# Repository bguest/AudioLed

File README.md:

# AudioLed
Board to drive a string of WS2801 chips using audio and a MSGEQ7

# Setup

## Attaching FTDI
The FTDI Cable plugs in under the 12v Power Connector. The FTDI Grounds are close to the center of
the board, the DTR is closer to the edge of the board.

If the power connector is in the upper right of the board facing up the FTDI pins will be

GND, GND, VCC, RXI, RXO, DTR

## Setting up Arduino and Compiling the Code (MAC)

1. Clone this repo to `~/Documents/Arduino` with `cd ~/Documents/Arduino && git clone git@github.com:bguest/AudioLed.git`
2. Change directory to AudioLED with `cd AudioLed`
3. Mod setup script `chmod +x setup.sh`
4. Run Setup `.\setup.sh` this will clone correct versions of `Adafruit_WS2801` and `Arduino-IRremote`
5. Download Arduino v1.6.6 (May not compile with later versions of Arduino)
6. Launch Arduino v1.6.6
7. Open AudioLED
8. Set board to `Arduino Pro or Pro Mini`
9. Set processor to `ATmega328 (5V, 16MHz)`
10. Verify and Upload Code

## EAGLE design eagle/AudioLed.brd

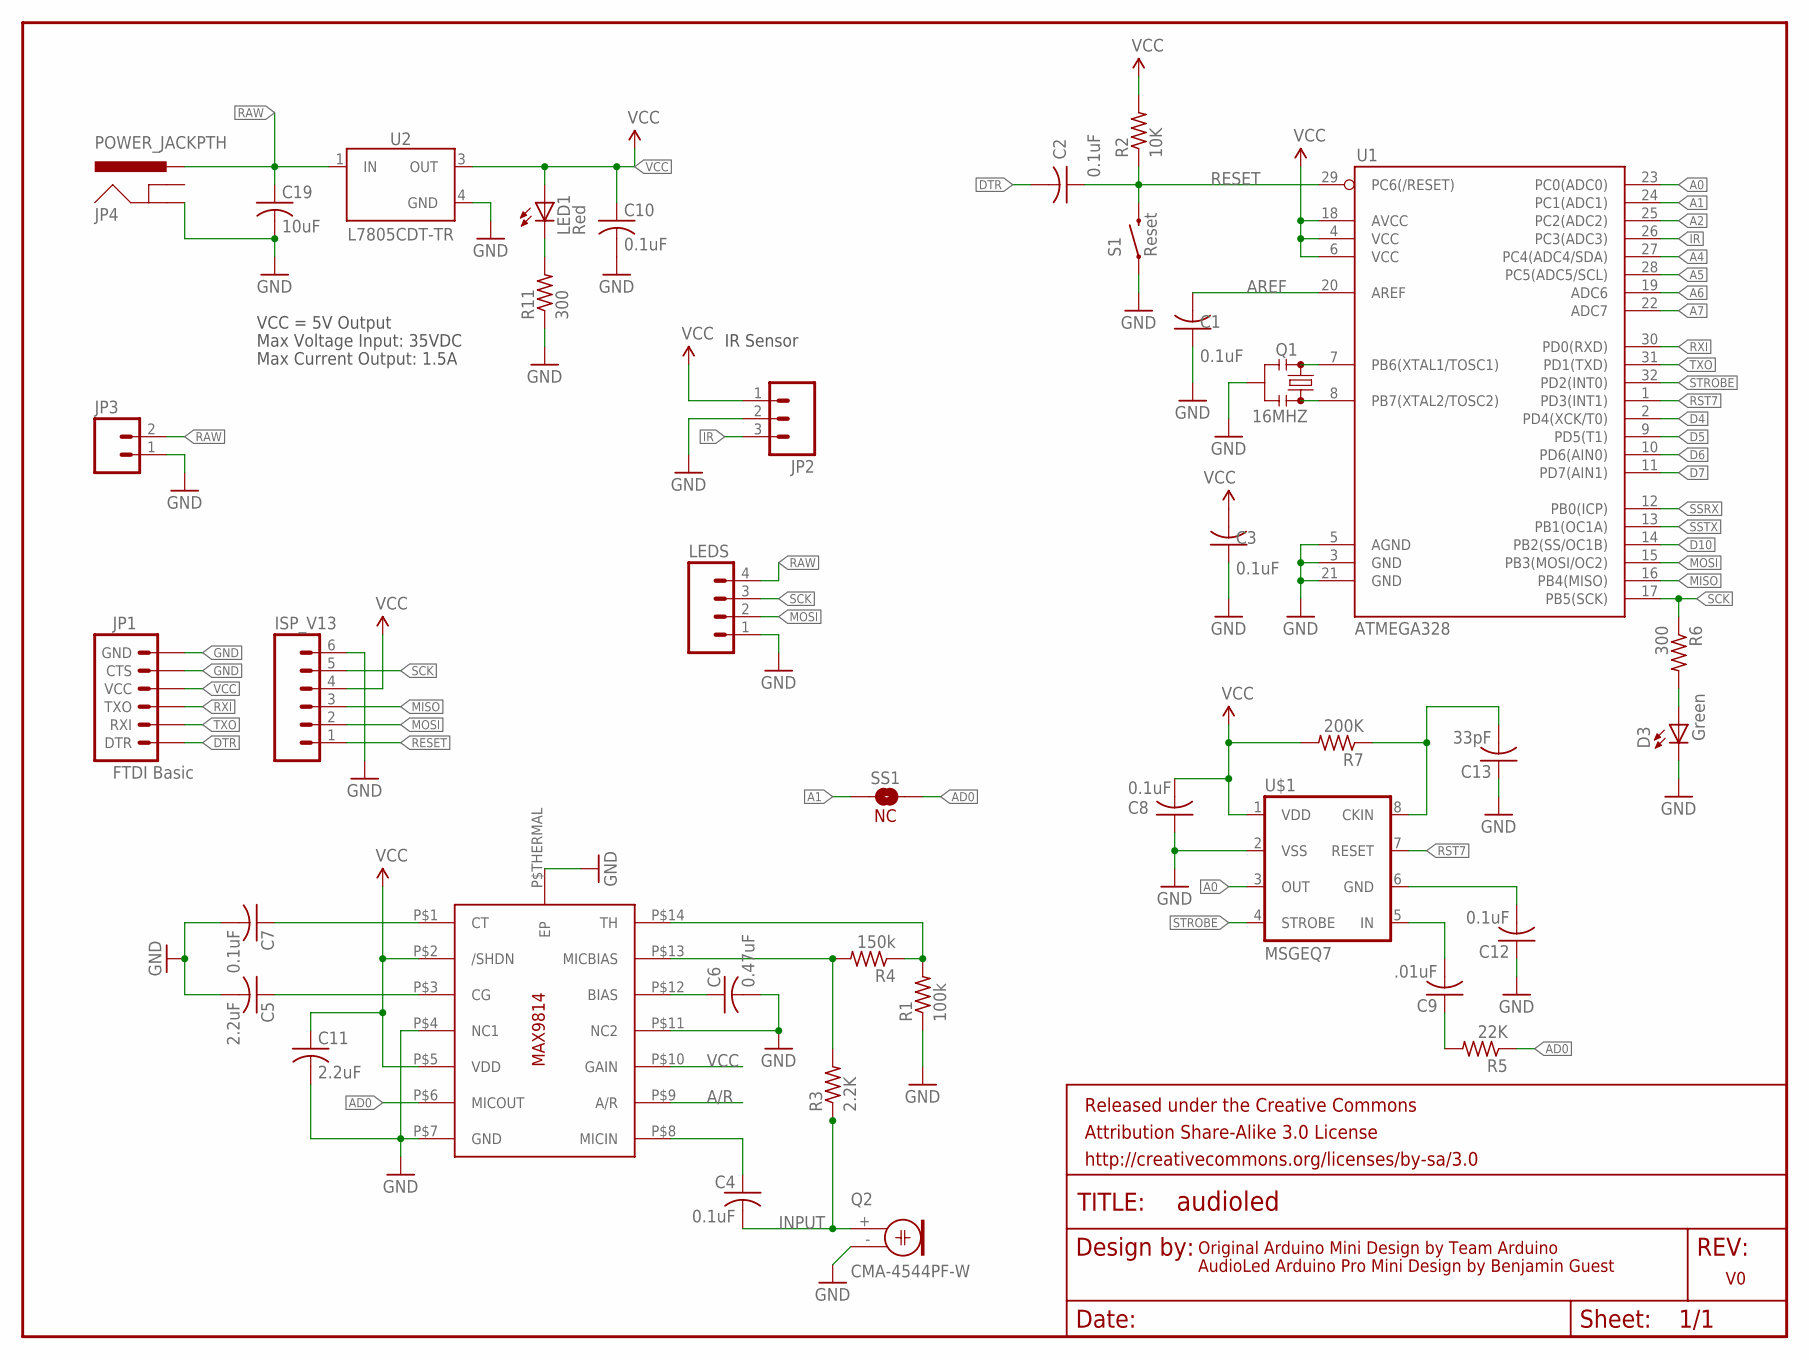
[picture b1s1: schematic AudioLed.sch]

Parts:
C1, C2, C3, C8, C10, C12: 0.1uF; C0805
C4, C7: 0.1uF; C0805K
C5, C11: 2.2uF; C0805K
C6: 0.47uF; C0805K
C9: .01uF; C0805
C13: 33pF; C0805
C19: 10uF; C0805
D3: Green; CHIPLED_0805
FRAME1: FRAME-LETTER; CREATIVE_COMMONS
ISP_V13: M06SIP; 1X06
JP1: FTDI Basic; 1X06
JP2: M03JST-PTH; JST-3-PTH
JP3: M02JST-PTH-2; JST-2-PTH
JP4: POWER_JACKPTH; POWER_JACK_PTH
LED1: Red; CHIPLED_0805
LEDS: M04JST-PTH; JST-4-PTH
Q1: 16MHZ; RESONATOR-SMD
Q2: CMA-4544PF-W; 9.7ELECTRET
R1: 100k; R0805
R2: 10K; M0805
R3: 2.2K; R0805
R4: 150k; R0805
R5: 22K; M0805
R6, R11: 300; M0805
R7: 200K; M0805
S1: Reset; TACTILE-SWITCH-SMD-ALT01
SS1: NC; SJ_2S
U1: ATMEGA328; TQFP32-08
U2: L7805CDT-TR; DPAK
U4: MAX9814TDFN14; TDFN14_3X3MM
U$1: MSGEQ7; DIL08-ROUND

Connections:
A0: U1.23 (PC0(ADC0)), U$1.3 (OUT)
A1: SS1.1, U1.24 (PC1(ADC1))
A2: U1.25 (PC2(ADC2))
A4: U1.27 (PC4(ADC4/SDA))
A5: U1.28 (PC5(ADC5/SCL))
A6: U1.19 (ADC6)
A7: U1.22 (ADC7)
A/R: U4.P$9 (A/R)
AD0: R5.1, SS1.2, U4.P$6 (MICOUT)
AREF: C1.2, U1.20 (AREF)
D4: U1.2 (PD4(XCK/T0))
D5: U1.9 (PD5(T1))
D6: U1.10 (PD6(AIN0))
D7: U1.11 (PD7(AIN1))
D10: U1.14 (PB2(SS/OC1B))
DTR: C2.2, JP1.1 (DTR)
GND: C1.1, C3.1, C5.2, C6.2, C7.2, C8.1, C10.2, C11.2, C12.1, C13.1, C19.2, D3.C, ISP_V13.6, JP1.5 (CTS), JP1.6 (GND), JP2.2, JP3.1, JP4.GND, LEDS.1, Q1.2, Q2.- (1), R1.1, R11.1, S1.1, S1.2 (1), U1.3 (GND), U1.5 (AGND), U1.21 (GND), U2.4 (GND), U4.P$4 (NC1), U4.P$7 (GND), U4.P$11 (NC2), U4.P$THERMAL (EP), U$1.2 (VSS)
INPUT: C4.2, Q2.+ (2), R3.1
IR: JP2.3, U1.26 (PC3(ADC3))
MISO: ISP_V13.3, U1.16 (PB4(MISO))
MOSI: ISP_V13.2, LEDS.2, U1.15 (PB3(MOSI/OC2))
unnamed: Q1.3, U1.8 (PB7(XTAL2/TOSC2))
unnamed: Q1.1, U1.7 (PB6(XTAL1/TOSC1))
unnamed: C6.1, U4.P$12 (BIAS)
unnamed: LED1.C, R11.2
unnamed: C4.1, U4.P$8 (MICIN)
unnamed: C9.1, R5.2
unnamed: D3.A, R6.2
unnamed: C7.1, U4.P$1 (CT)
unnamed: C5.1, U4.P$3 (CG)
unnamed: R1.2, R4.1, U4.P$14 (TH)
unnamed: R3.2, R4.2, U4.P$13 (MICBIAS)
unnamed: C9.2, U$1.5 (IN)
unnamed: C12.2, U$1.6 (GND)
unnamed: C13.2, R7.1, U$1.8 (CKIN)
RAW: C19.1, JP3.2, JP4.PWR, LEDS.4, U2.1 (IN)
RESET: C2.1, ISP_V13.1, R2.1, S1.3 (2), S1.4 (2), U1.29 (PC6(/RESET))
RST7: U1.1 (PD3(INT1)), U$1.7 (RESET)
RXI: JP1.3 (TXO), U1.30 (PD0(RXD))
SCK: ISP_V13.5, LEDS.3, R6.1, U1.17 (PB5(SCK))
SSRX: U1.12 (PB0(ICP))
SSTX: U1.13 (PB1(OC1A))
STROBE: U1.32 (PD2(INT0)), U$1.4 (STROBE)
TXO: JP1.2 (RXI), U1.31 (PD1(TXD))
VCC: C3.2, C8.2, C10.1, C11.1, ISP_V13.4, JP1.4 (VCC), JP2.1, LED1.A, R2.2, R7.2, U1.4 (VCC), U1.6 (VCC), U1.18 (AVCC), U2.3 (OUT), U4.P$2 (/SHDN), U4.P$5 (VDD), U4.P$10 (GAIN), U$1.1 (VDD)

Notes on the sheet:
Original Arduino Mini Design by Team Arduino
AudioLed Arduino Pro Mini Design by Benjamin Guest
Max Voltage Input: 35VDC
Max Current Output: 1.5A
VCC = 5V Output
IR Sensor

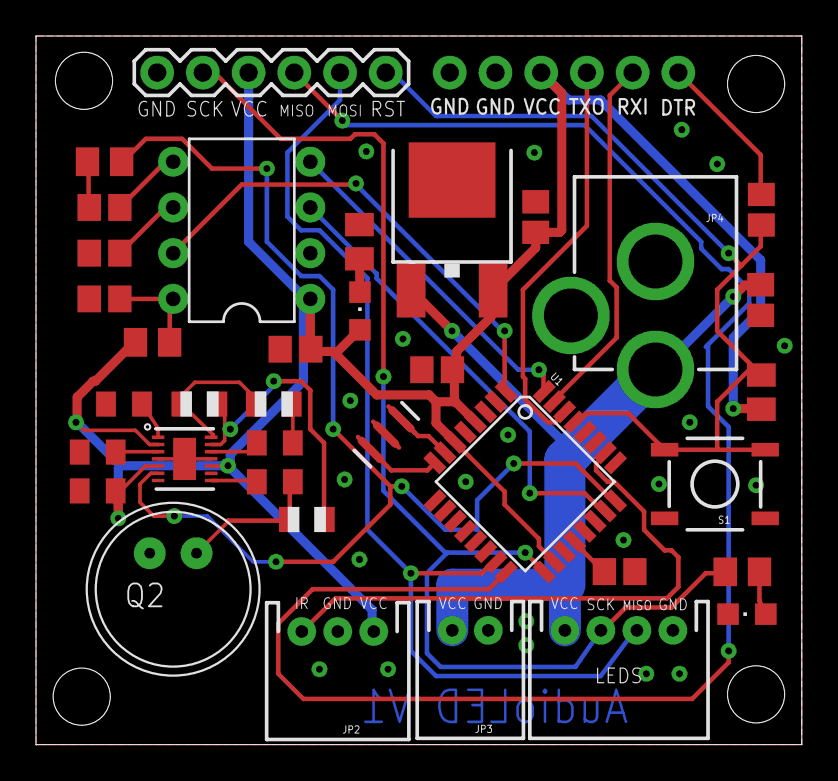
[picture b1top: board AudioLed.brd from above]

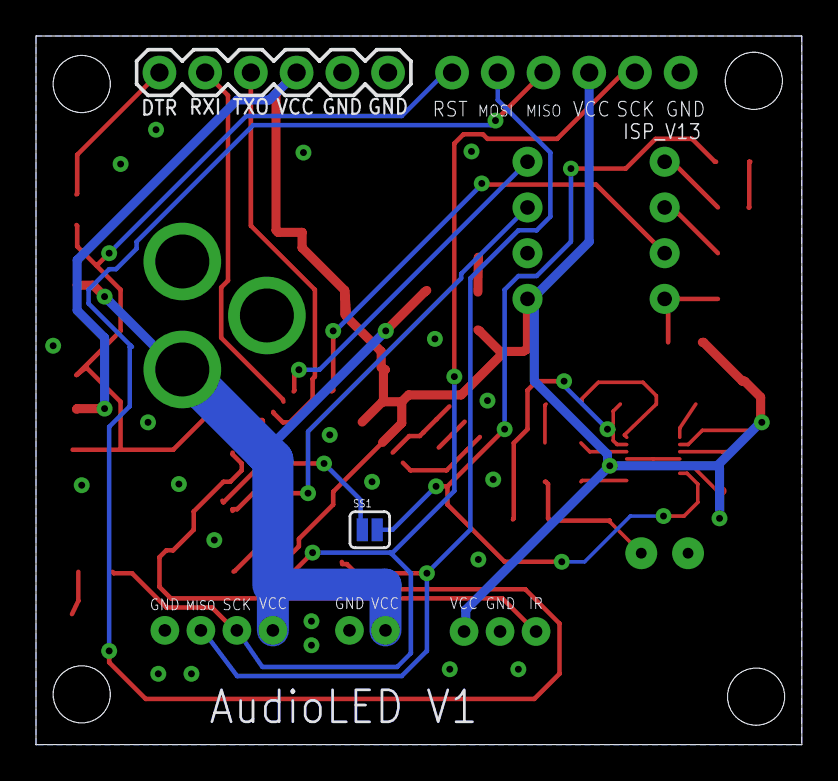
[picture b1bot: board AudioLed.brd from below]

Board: 2 copper layers, 42.5 x 39.4 mm, 39 parts (2 on the bottom side), 32 nets.

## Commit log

2016-01-05 Board
2016-01-05 Fix Incorrectly Labled Capacitor
2016-01-06 Add Dimensions
2016-01-25 Move trace slightly
2016-01-25 Replace bad resonator with SparkFun Resonator
2016-02-14 WIP: Add Code
2016-02-14 Add Sound
2016-02-15 Add Spectrum0
2016-02-16 Add Wander
2016-02-18 Add Tempo and IR
2016-02-19 Add Wave Equation
2016-02-19 Add Hue array, fix tempo button
2016-02-20 Move Remote to its own class (untested)
2016-02-21 Add Influence (untested)
2016-02-21 Add Cnter Pulse (untested)
2016-02-22 Fixes to untested
2016-02-23 Switch to hsv calculations add drizly color switch
2016-02-23 change wave boundary to neuman
2016-02-24 Add Pixel Direction
2016-02-25 Sound Collect
2016-02-25 Switch to RollOff
2016-02-25 Improvements to TwoColor
2016-03-01 Add Visual For Current Push Layer
2016-03-03 TimeDomain
2016-03-03 Tweaks
2016-03-04 Add Configurations
2016-03-11 Add Serveral new configs
2016-03-15 Add ParticleSystem
2016-03-19 Add Down Force to wave
2016-03-21 Add CellularAutomata and things
2016-04-04 Add Second Remote, Add Configs
2016-04-10 Add Strobe Effect
2016-04-10 New TwoColor input inprovements
2016-04-11 Add CenterSquare
2016-04-11 'Fix' CenterSquare
2016-04-15 Move things around
2016-04-16 Bump Board Version to V1
2016-04-19 Add USE_RAW_VOLUME
2016-04-20 Improvements to CenterSquare
2016-04-20 Simplification?
2016-04-22 Add Bubbles
2016-04-24 Fix Remote
2016-04-29 Notes
2016-07-21 Change default to center wave
2016-09-17 Splotches: WIP
2016-10-25 Add setup.sh and setup instructions
2016-10-27 Small Tweeks
2016-11-07 Add Solid Color Config
2017-01-27 Update to use with 1.8.1, add ablity to move center pulse

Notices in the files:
parts and their libraries:
SparkFun-Aesthetics: Licensing: CC v3.0 Share-Alike You are welcome to use this library for commercial purposes.
SparkFun-Aesthetics: Released under the Creative Commons Attribution Share-Alike 3.0 License
SparkFun-Aesthetics: http://creativecommons.org/licenses/by-sa/3.0
